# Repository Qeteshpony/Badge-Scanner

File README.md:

# NFC-Badge Scanner

[Hardware Documentation](https://qeteshpony.github.io/Badge-Scanner)

Raspberry Pi Pico W powered device to scan NFC-Badges and show a status on display

It is meant to be used with the widely available RFID-RC522 reader and the [DFROBOT LCD1602 RGB Backlight Module](https://raw.githubusercontent.com/DFRobot/DFRobot_RGBLCD/master/DFR0464%20Datasheet.pdf) but any other I2C Display should work as well. 

The device features an [I2C RTC](https://www.analog.com/media/en/technical-documentation/data-sheets/ds3231m.pdf) with backup battery connector and an SD-Card reader connected via SPI for data storage. 

There is also a buzzer that can be used for audible signals. 

Power can be provided through the USB port of the Pico or through a LiPo battery connected to the board. The LiPo battery can also be charged via the USB port and the device will switch seamlessly between battery and usb power.

The button can be used to send a shutdown signal to the microcontroller which then can power the whole device off by pulling a GPIO low. Pressing the button while the device is off or pluggin in USB will power it up again.

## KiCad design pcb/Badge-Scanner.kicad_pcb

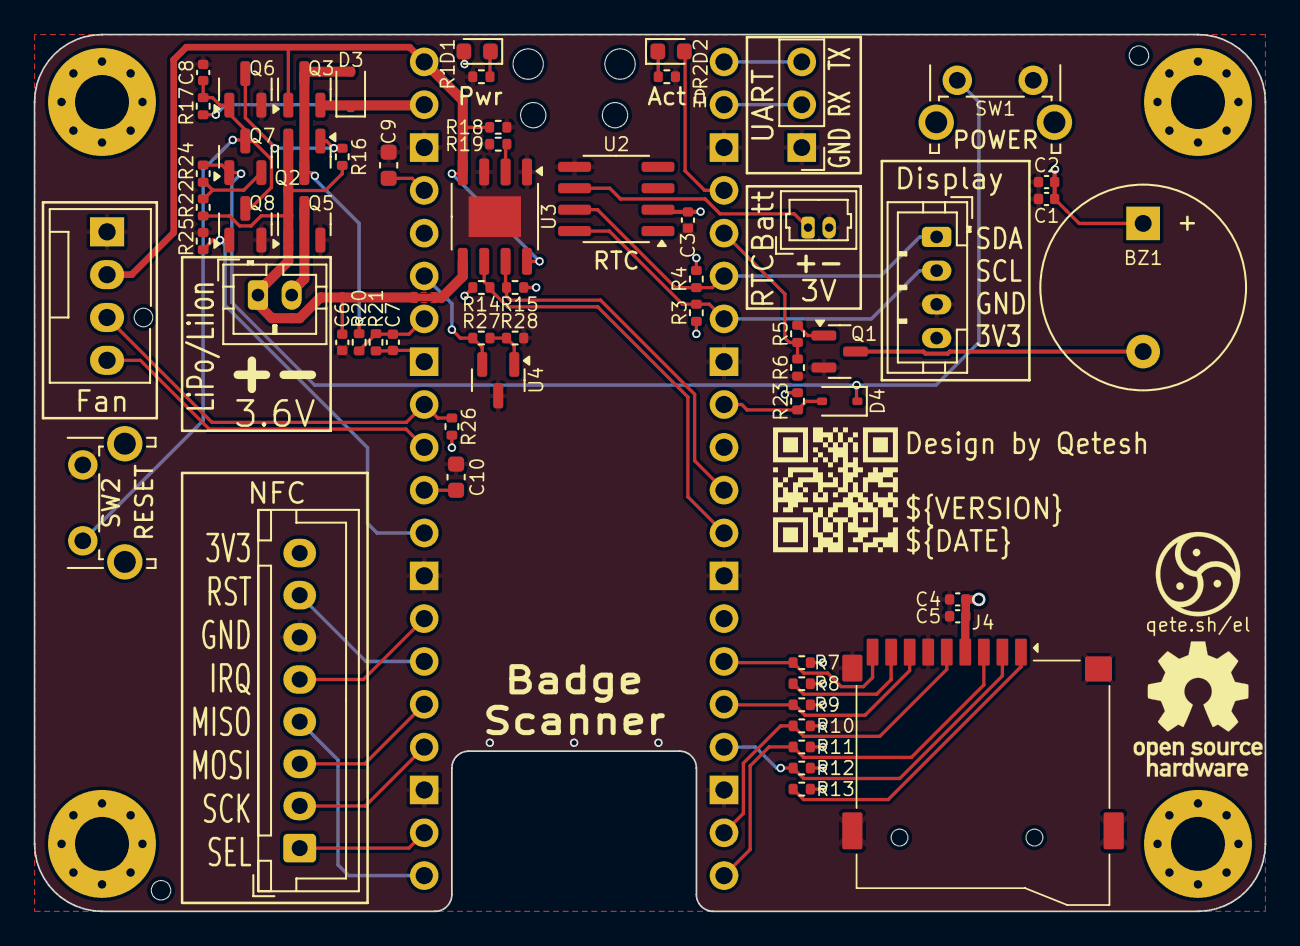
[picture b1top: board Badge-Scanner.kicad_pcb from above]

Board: 2 copper layers, 73.0 x 52.0 mm, 63 parts (1 on the bottom side), 48 nets.

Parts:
BT1: Battery_Cell; Molex_PicoBlade_53047-0210_1x02_P1.25mm_Vertical
BT2: 18650; JST_PH_B2B-PH-K_1x02_P2.00mm_Vertical
BZ1: Buzzer; Buzzer_12x9.5RM7.6
C1, C3, C5, C7: 100n; C_0402_1005Metric
C2, C4, C6, C8: 10u; C_0402_1005Metric
C9, C10: 22u; C_0603_1608Metric
D1: Power; LED_0603_1608Metric
D2: Activity; LED_0603_1608Metric
D3, D4: 1N5819WS; D_SOD-323
J1: NFC-Module; JST_XH_B8B-XH-A_1x08_P2.50mm_Vertical
J2: Serial; PinHeader_1x03_P2.54mm_Vertical
J3: I2C; JST_PH_B4B-PH-K_1x04_P2.00mm_Vertical
J4: Micro_SD_Card_Det1; TF_PUSH_Micro-SD-Connector
M1: Fan; FanPinHeader_1x04_P2.54mm_Vertical
Q1, Q5, Q6, Q8: AO3400A; SOT-23
Q2, Q3, Q7: AO3401A; SOT-23
R1, R2: 680R; R_0402_1005Metric
R3, R4, R19, R27: 2k; R_0402_1005Metric
R5: 100R; R_0402_1005Metric
R6, R18, R20, R21, R23, R24: 100k; R_0402_1005Metric
R7, R8, R9, R10, R11, R12, R13: 3k3; R_0402_1005Metric
R14, R15, R25, R26, R28: 10k; R_0402_1005Metric
R16, R17: 1M; R_0402_1005Metric
R22: 1k; R_0402_1005Metric
SW1: Power; SW_Tactile_SPST_Angled_PTS645Vx58-2LFS
SW2: Reset; SW_Tactile_SPST_Angled_PTS645Vx31-2LFS
U1: Pico W; RPi_PicoW_SMD_TH_NoSilkscreenText
U2: DS3231MZ; SOIC-8_3.9x4.9mm_P1.27mm
U3: TP4056; HSOP-8-1EP_3.9x4.9mm_P1.27mm_EP2.41x3.1mm
U4: CJ431; SOT-23

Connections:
+3V3: BZ1.1 (+), C1.2, C2.2, C3.2, C4.2, C5.2, D1.2 (A), J1.8, J3.4, J4.4 (VDD), R3.2, R4.2, R7.1, R8.1, R9.1, R10.1, R11.1, R12.1, R13.1, R14.1, R15.1, R23.1, R26.1, U1.36 (3V3), U2.2 (VCC)
/3V3_EN: C9.2, U1.37 (3V3_EN)
/ADC_VREF: R27.1, U1.35 (ADC_VREF), U4.2 (K)
/BZ-: BZ1.2 (-), Q1.3 (D)
/BattPwrOff: Q8.1 (G), R25.2, U1.29 (GP22)
/BattVolt: C7.1, R20.2, R21.1, U1.34 (GP28)
/Battery Management/Batt+: BT2.1 (+), C6.1, Q2.2 (S), Q5.1 (G), R16.1, R22.1, U3.5 (BAT)
/Battery Management/Batt-: BT2.2 (-), Q5.3 (D)
/Battery Management/BattSw: C8.1, Q6.1 (G), Q7.3 (D), Q8.3 (D), R17.2, SW2.1
/Battery Management/BattSwG: Q2.1 (G), Q6.3 (D), R16.2
/Battery Management/BattSwd: D3.2 (A), Q2.3 (D), Q3.3 (D), R20.1
/Battery Management/PROG: R19.1, U3.2 (PROG)
/Battery Management/SW1: D4.1 (K), Q7.1 (G), R24.2, SW1.1
/Buzzer: R5.1, R6.1, U1.5 (GP3)
/FAN_PWM: M1.4 (PWM), U1.31 (GP26)
/FAN_TACHO: M1.3 (Tacho), R26.2, U1.32 (GP27)
/LED: D2.2 (A), U1.4 (GP2)
/NFC_CS: J1.1, U1.22 (GP17)
/NFC_IRQ: J1.5, U1.27 (GP21)
/NFC_MISO: J1.4, U1.21 (GP16)
/NFC_MOSI: J1.3, U1.25 (GP19)
/NFC_RST: J1.7, U1.26 (GP20)
/NFC_SCK: J1.2, U1.24 (GP18)
/RTC_VBAT: BT1.1 (+), U2.6 (VBAT)
/RUN: C10.2, U1.30 (RUN)
/SCL: J3.2, R3.1, U1.7 (GP5), U2.8 (SCL)
/SDA: J3.1, R4.1, U1.6 (GP4), U2.7 (SDA)
/SDCard/DAT1: J4.8 (DAT1), R8.2
/SDCard/DAT2: J4.1 (DAT2), R13.2
/SD_CS: J4.2 (DAT3/CD), R12.2, U1.17 (GP13)
/SD_DET: J4.9 (DET), R7.2, U1.15 (GP11)
/SD_MISO: J4.7 (DAT0), R9.2, U1.16 (GP12)
/SD_MOSI: J4.3 (CMD), R11.2, U1.20 (GP15)
/SD_SCK: J4.5 (CLK), R10.2, U1.19 (GP14)
/UART0RX: J2.2, U1.2 (GP1)
/UART0TX: J2.3, U1.1 (GP0)
/~Button: D4.2 (A), R23.2, U1.9 (GP6)
/~ChargeActive: R15.2, U1.11 (GP8), U3.7 (~CHRG)
/~ChargeStdby: R14.2, U1.12 (GP9), U3.6 (~STDBY)
GND: BT1.2 (-), C1.1, C2.1, C3.1, C4.1, C5.1, C6.2, C8.2, C9.1, C10.1, J1.6, J2.1, J3.3, J4.6 (VSS), J4.10 (SHIELD), M1.1 (-), Q1.2 (S), Q5.2 (S), Q6.2 (S), Q8.2 (S), R1.2, R2.2, R6.2, R18.2, R19.2, R25.1, R28.2, SW1.2, SW2.2, U1.3 (GND), U1.8 (GND), U1.13 (GND), U1.18 (GND), U1.23 (GND), U1.28 (GND), U1.38 (GND), U2.5 (GND), U3.1 (TEMP), U3.3 (GND), U3.9 (EP), U4.3 (A)
GNDA: C7.2, R21.2, U1.33 (AGND)
unnamed: D1.1 (K), R1.1
unnamed: D2.1 (K), R2.1
unnamed: Q1.1 (G), R5.2
unnamed: Q7.2 (S), R22.2, R24.1
unnamed: R27.2, R28.1, U4.1 (REF)
VBUS: M1.2 (+), Q3.1 (G), R18.1, U1.40 (VBUS), U3.4 (VCC), U3.8 (CE)
VSYS: D3.1 (K), Q3.2 (S), R17.1, U1.39 (VSYS)

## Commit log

2024-06-16 feat: initial commit
2024-06-16 chore(main): release 1.0.0
2024-06-16 style: add JLC order number position
2024-06-16 fix: part numbers for connectors
2024-06-16 chore(main): release 1.0.1
2024-09-26 feat: add LiPo Circuitry
2024-09-26 ci: remove dependency between jobs
2024-09-26 style: silk screen cleanup
2024-09-27 fix: replace buzzer footprint
2024-09-27 feat: place power button on the board
2024-09-27 fix: add FET to measurement circuit
    Disable the battery measurement circuit when the device is switched off to save energy
2024-09-27 docs: add new features to README
2024-10-02 fix: power switch circuit capacitance
2024-10-03 style: enlarge pin description text
2024-10-03 style: add some netclasses for schematic clarity
2024-10-03 style: silkscreen improvements
2024-10-03 ci: add bottom render
2024-10-03 fix: remove wrong order number from SW1
2024-10-03 ci: new format
2024-10-03 ci: kibot
2024-10-04 ci: missed an option
2024-10-04 docs: add bottom view
2024-10-05 feat: optional fan connector
    feat: add 3V reference for ADC
2024-10-10 fix: change resistor values for batt measurement
2024-10-10 chore(main): release 1.1.0
2024-10-10 ci: update kibot release
2024-10-11 fix: turn around UART connector
2024-10-17 chore: delete old, leftover file
2024-10-17 fix: move power LED to 3.3V rail
    VSYS is too unstable since its voltage changes a lot between usb and battery powered mode
2024-10-17 chore(main): release 1.1.1
2024-10-21 fix: move measurement to BattSwd
2024-10-21 fix: add caps to delay startup of mcu
    Sometimes the mcu does not boot correctly when usb gets connected while the system is off - most likely because the flash does not get enough power quick enough. Adding a startup delay for the 3V3 re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
2025-01-07 feat: add reset button
2025-01-07 chore(main): release 1.2.0
2025-01-07 fix: re-release because of CI error
2025-01-07 chore(main): release 1.2.1
